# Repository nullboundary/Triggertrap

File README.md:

# Triggertrap Source Code

Triggertrap is an open-source camera triggering platform based on Arduino. 

It comes in two versions: Triggertrap v1 (TTv1), which is a device aimed at consumers; and Triggertrap Shield for Arduino (TT-k) which is aimed at advanced users, hackers, and geeks (like us!). 

The codebase you are looking at is for both the above devices. 

_NOTE_ - there *are* differences between the TTv1 and TT-k. By default, the code ships for the Triggertrap Shield for Arduino (TT-k), because we anticipate that most people downloading and using this code will be using the Triggertrap Shield. If you wish to compile and install this code on your TTv1 device, remember to go into TTConfig.h, and read the section *Choose your version of the Triggertrap*. 

## Triggertrap v1 (TTv1)

The Triggertrap v1 is a battery-powered device with several sensors built-in:

* Laser sensor
* Ambient Light sensor
* Sound sensor

It also has a fully configurable AUX port, in the shape of a RCA socket, designed to accept additional external inputs and sensors. 

_Form Factor_ - The Triggertrap v1 comes in a perspex casing, and uses touch-sensitive buttons for control and operation. 

## Triggertrap Shield for Arduino (TT-k)

The Triggertrap Shield for Arduino is an Arduino-powered device with several sensors built-in:

* Laser sensor
* Ambient Light sensor
* Sound sensor

It also has a fully configurable AUX port, in the shape of a RCA socket, designed to accept additional external inputs and sensors. 

_Form Factor_ - The Triggertrap Shield for Arduino is an Arduino shield, and uses physical buttons for its interface. 

# Open Source & Licencing information 

This file is part of Triggertrap. See Triggertrap.com for more information.

Triggertrap is free software: you can redistribute it and/or modify it under the terms of the GNU General Public License as published by the Free Software Foundation, either version 3 of the License, or (at your option) any later version.
 
Triggertrap is distributed in the hope that it will be useful, but WITHOUT ANY WARRANTY; without even the implied warranty of MERCHANTABILITY or FITNESS FOR A PARTICULAR PURPOSE.  See the GNU General Public License for more details.

You should have received a copy of the GNU General Public License along with Triggertrap. If not, see <http://www.gnu.org/licenses/>.

## Restrictions

The only thing we are keeping control over is the Triggertrap trademarks (name and logo). Full details of the Triggertrap licence is available on http://triggertrap.com/license/ 

# Changenotes

## 0.3.36 (6 March 2013)
* Bugfix: IR signal overflow fix for Nikon cameras when using shield only.
* Bugfix: Adjustment to IR timings for Sony cameras.
* Enhancement: Integration of Timelapse modifications from Duane Cassone. 

## 0.3.35 (16 July 2012)

* Bugfix: Fixes a tiny bug where the screen contrast (menu option added in 0.3.35) wasn't saved to EEPROM properly. 
* Bugfix: Elegant little hack that reads the LCD contrast setting twice, discarding the first reading, ensuring that the readings are accurate, especially when Triggertrap wakes from sleep. 
* Tagging with 0.3.35

## 0.3.34 (9 July 2012)

* Formally introduces Bulb Ramping into the Triggertrap Firmware
* Adds a menu item for adjusting your screen contrast for TTv1 (System -> Contrast)
* Bugfix: Fixes sleep problem introduced in 0.3.33b
* Tidies up code in TriggerTrap.cpp for easier hackability & readability

## 0.3.33b (18 June 2012)

* Introduces the Bulb Ramping feature
* Breaks several other features ;) (that is why this version was only ever a beta...)

## 0.3.32 (23 March 2012)

* Fixes a bug in the production Triggertrap where the laser sensor was too sensitive
* Fixes a bug in the production Triggertrap where the LCD display came up way too dark
* Adds additional documentation licence information that was missed out in the initial release
* Removes accidentally included .DS_Store files

## 0.3.31 (21 March 2012)

First open-source release of the Triggertrap codebase.

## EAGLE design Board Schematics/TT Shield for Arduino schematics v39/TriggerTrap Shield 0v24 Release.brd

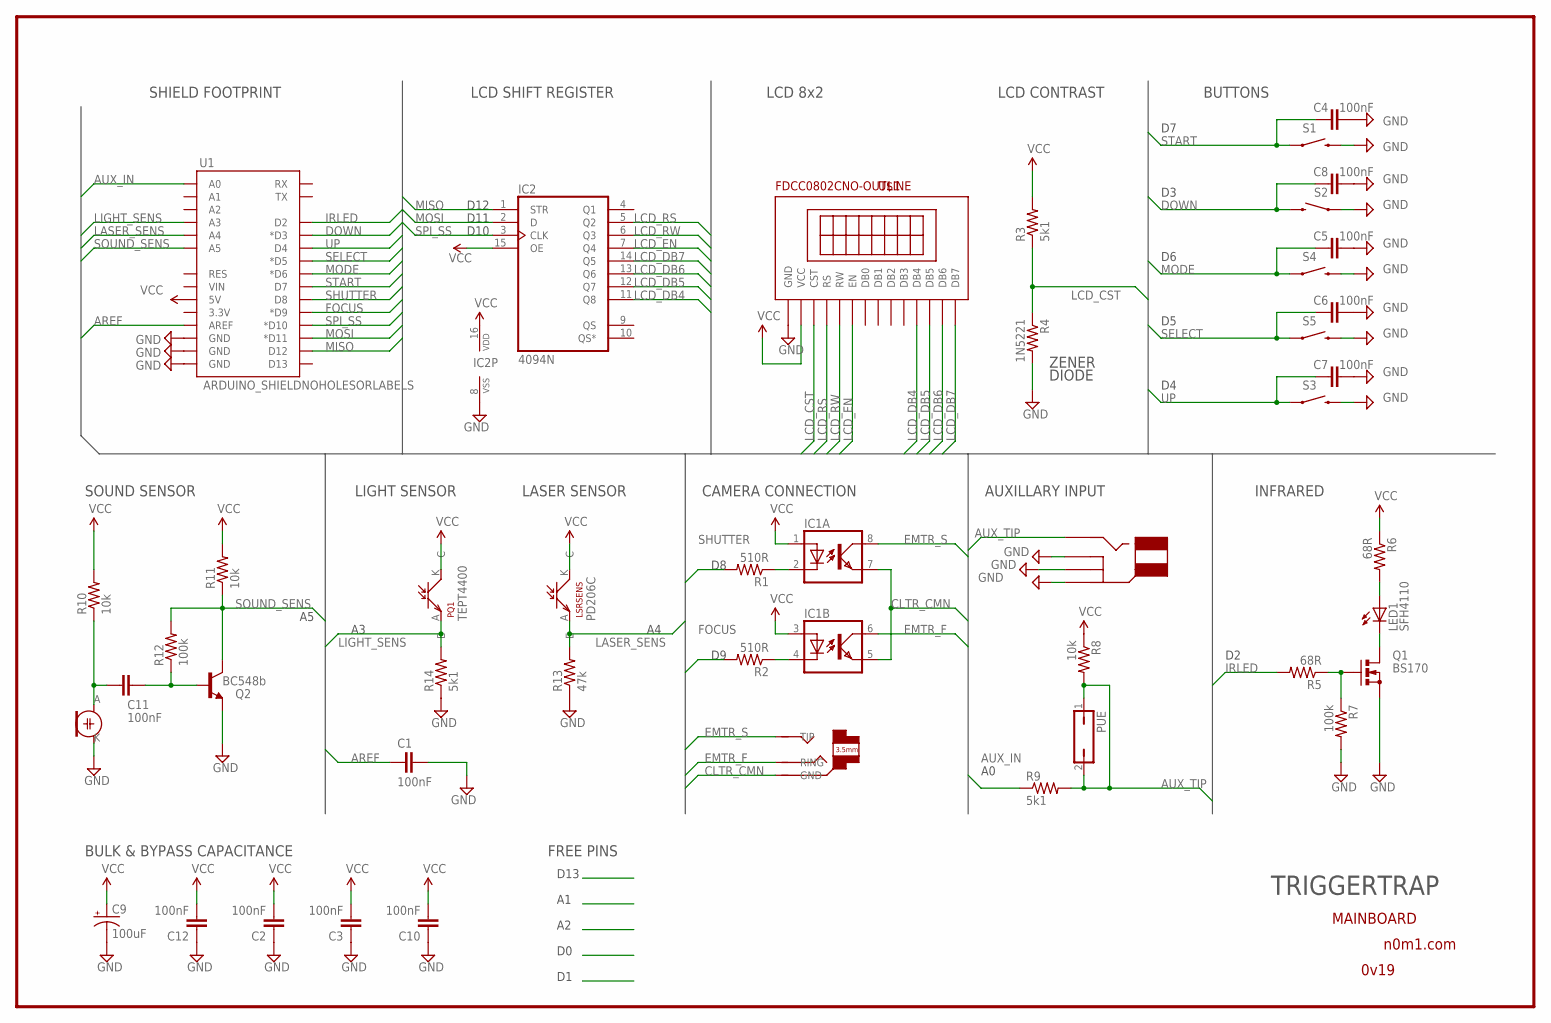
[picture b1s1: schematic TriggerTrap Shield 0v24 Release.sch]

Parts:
AUX: CUI_RCJ-017-RCA; RCA_CUI_RCJ-017
C1, C2, C3, C4, C5, C6, C7, C8, C10, C11, C12: 100nF; C050-024X044
C9: 100uF; TT2D7L
CAM: AUDIO_3.5MM_L_3523; AUDIO_3.5MM_LONG
IC1: LTV826SMLPADS; DIL08-SMLPADS
IC2: 4094N; DIL16
LED1: SFH4110; SIDE_LED
LSRSENS: PD204-6C; LSR-SNS-3MM
MIC: MIC; MIC-254-ECM94-RO
PQ1: TEPT4400; LED-3MM
PUE: JP1Q; JP1
Q1: BS170; SOT54E
Q2: BC548b; SOT54E
R1, R2: 510R; 0204/5
R3, R9, R14: 5k1; 0204/5
R4: 1N5221; 0204/5
R5, R6: 68R; 0204/5
R7, R12: 100k; 0204/5
R8, R10, R11: 10k; 0204/5
R13: 47k; 0204/5
S1: SWITCH-MOMENTARY-212MM; TACTILE-PTH-12MM
S2, S3, S4, S5: SWITCH-MOMENTARY-2PTH; TACTILE-PTH
U1: ARDUINO_SHIELDNOHOLESORLABELS; DUEMILANOVE_SHIELD_NOHOLES_NOLABELS
U$1: FDCC0802CNO-OUTLINE; 8X2-TOPLCD-NOOUTLINE

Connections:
AREF: C1.2, U1.AREF
AUX_IN: R9.1, U1.A0
AUX_TIP: AUX.P$4 (TIP), PUE.1, PUE.2, R8.2, R9.2
CLTR_CMN: CAM.P$1 (GND), IC1.5 (EMIT), IC1.7 (EMIT)
DOWN: C8.1, S2.3 (2), U1.D3 (*D3)
EMTR_F: CAM.P$3 (RING), IC1.6 (COL)
EMTR_S: CAM.P$2 (TIP), IC1.8 (COL)
FOCUS: R2.2, U1.D9 (*D9)
GND: AUX.P$1 (GND1), AUX.P$2 (GND2), AUX.P$3 (GND), C1.1, C2.1, C3.1, C4.2, C5.2, C6.2, C7.2, C8.2, C9.-, C10.1, C12.1, IC2.8 (VSS), MIC.K, Q1.S, Q2.S (E), R4.2, R7.2, R13.1, R14.1, S1.3 (2), S2.1, S3.3 (2), S4.3 (2), S5.3 (2), U1.GND@0 (GND), U1.GND@1 (GND), U1.GND@2 (GND), U$1.P$1 (GND)
IRLED: R5.2, U1.D2
LASER_SENS: LSRSENS.A (E), R13.2, U1.A4
LCD_CST: R3.1, R4.1, U$1.P$3 (CST)
LCD_DB4: IC2.11 (Q8), U$1.P$11 (DB4)
LCD_DB5: IC2.12 (Q7), U$1.P$12 (DB5)
LCD_DB6: IC2.13 (Q6), U$1.P$13 (DB6)
LCD_DB7: IC2.14 (Q5), U$1.P$14 (DB7)
LCD_EN: IC2.7 (Q4), U$1.P$6 (EN)
LCD_RS: IC2.5 (Q2), U$1.P$4 (RS)
LCD_RW: IC2.6 (Q3), U$1.P$5 (RW)
LIGHT_SENS: PQ1.A (E), R14.2, U1.A3
MISO: IC2.1 (STR), U1.D12
MODE: C5.1, S4.1, U1.D6 (*D6)
MOSI: IC2.2 (D), U1.D11 (*D11)
unnamed: C11.1, MIC.A, R10.1
unnamed: LED1.K (C), Q1.D
unnamed: LED1.A, R6.2
unnamed: Q1.G, R5.1, R7.1
unnamed: C11.2, Q2.G (B), R12.1
unnamed: IC1.4 (C), R2.1
unnamed: IC1.2 (C), R1.1
SELECT: C6.1, S5.1, U1.D5 (*D5)
SHUTTER: R1.2, U1.D8
SOUND_SENS: Q2.D (C), R11.1, R12.2, U1.A5
SPI_SS: IC2.3 (CLK), U1.D10 (*D10)
START: C4.1, S1.1, U1.D7
UP: C7.1, S3.1, U1.D4
VCC: C2.2, C3.2, C9.+, C10.2, C12.2, IC1.1 (A), IC1.3 (A), IC2.15 (OE), IC2.16 (VDD), LSRSENS.K (C), PQ1.K (C), R3.2, R6.1, R8.1, R10.2, R11.2, U1.5V, U$1.P$2 (VCC)

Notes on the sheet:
BULK & BYPASS CAPACITANCE
CAMERA CONNECTION
INFRARED
AUXILLARY INPUT
TRIGGERTRAP
MAINBOARD
n0m1.com
0v19
D10
D11
D12
SHIELD FOOTPRINT
LCD 8x2
LCD CONTRAST
LCD SHIFT REGISTER
SOUND SENSOR
LASER SENSOR
LIGHT SENSOR
BUTTONS
FREE PINS
D13
ZENER
DIODE
TEPT4400
PD206C

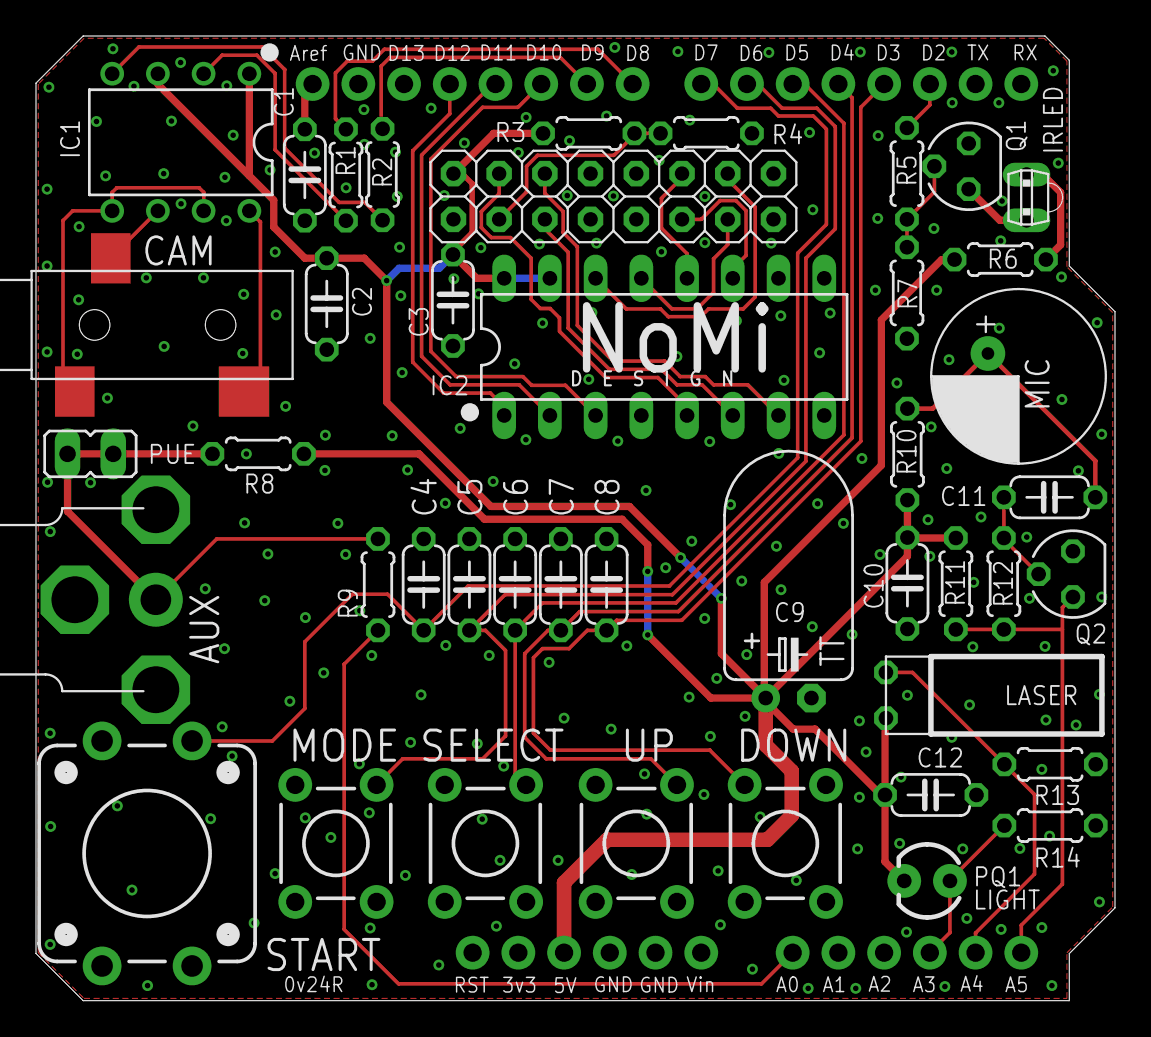
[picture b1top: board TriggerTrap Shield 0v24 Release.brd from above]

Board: 2 copper layers, 59.9 x 53.6 mm, 44 parts (1 on the bottom side), 37 nets.

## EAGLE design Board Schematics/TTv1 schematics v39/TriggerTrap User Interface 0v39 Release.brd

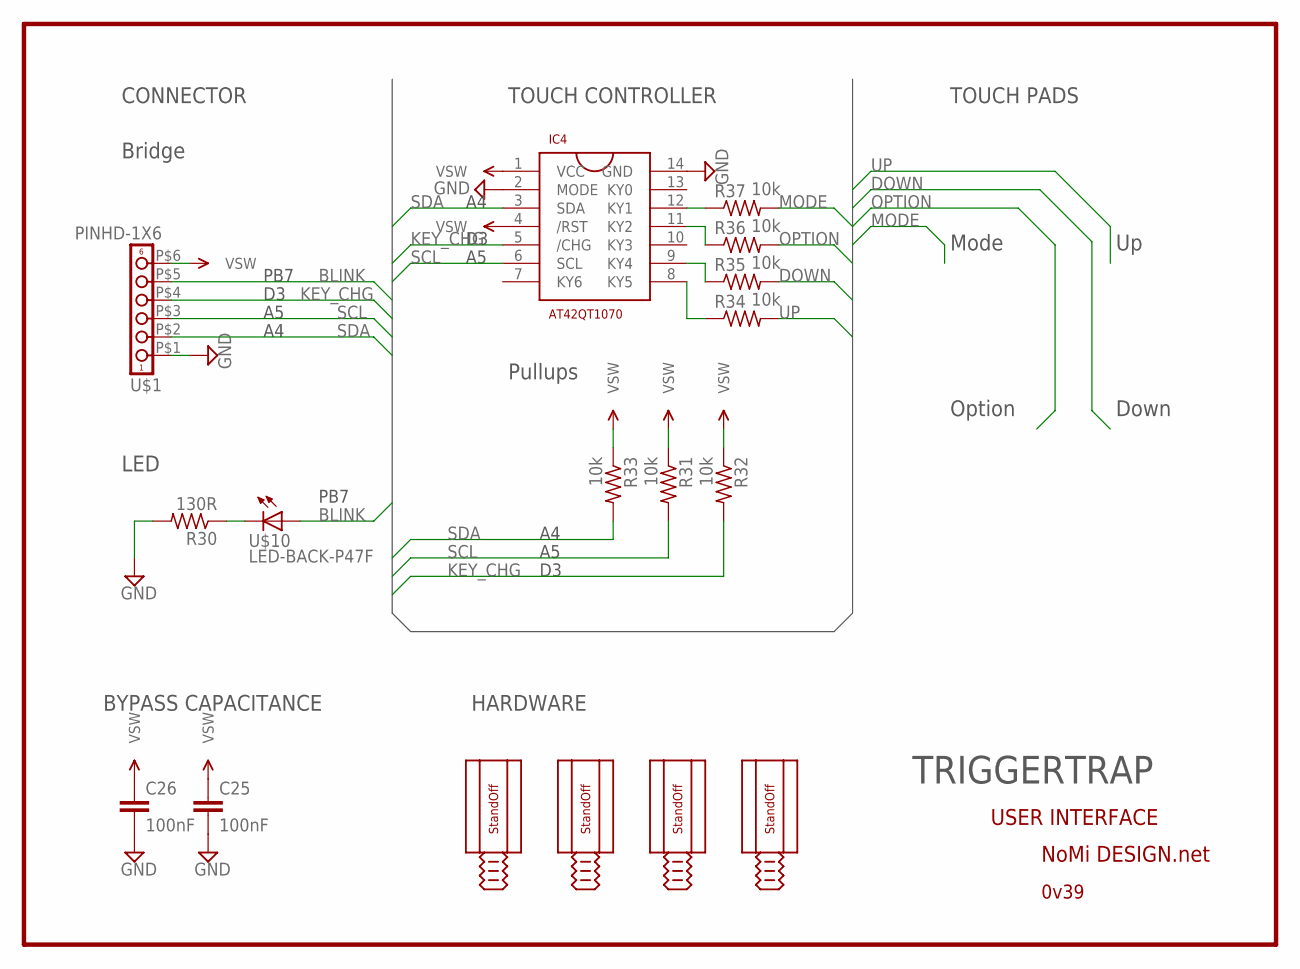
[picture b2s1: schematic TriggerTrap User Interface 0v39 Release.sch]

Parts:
C25, C26: 100nF; C0603K
IC4: AT42QT1070; 14SOIC
R30: 130R; R0603
R31, R32, R33, R34, R35, R36, R37: 10k; R0603
U$1: PINHD-1X6; PINHD-1X6-SMD
U$2, U$23, U$24, U$25: STAND-0FF-3.2; STAND-OFF
U$10: LED-BACK-P47F; LED-P47F

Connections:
BLINK: U$1.P$5 (5), U$10.A
DOWN: R35.2
GND: C25.2, C26.2, IC4.2 (MODE), IC4.14 (GND), R30.2, U$1.P$1 (1)
KEY_CHG: IC4.5 (/CHG), R32.2, U$1.P$4 (4)
MODE: R37.2
unnamed: IC4.12 (KY1), R37.1
unnamed: IC4.11 (KY2), R36.1
unnamed: IC4.9 (KY4), R35.1
unnamed: IC4.8 (KY5), R34.1
unnamed: R30.1, U$10.C
OPTION: R36.2
SCL: IC4.6 (SCL), R31.2, U$1.P$3 (3)
SDA: IC4.3 (SDA), R33.2, U$1.P$2 (2)
UP: R34.2
VSW: C25.1, C26.1, IC4.1 (VCC), IC4.4 (/RST), R31.1, R32.1, R33.1, U$1.P$6 (6)

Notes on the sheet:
Bridge
HARDWARE
BYPASS CAPACITANCE
TOUCH CONTROLLER
LED
TRIGGERTRAP
USER INTERFACE
NoMi DESIGN.net
0v39
PB7
CONNECTOR
TOUCH PADS
Mode
Down
Option
Pullups

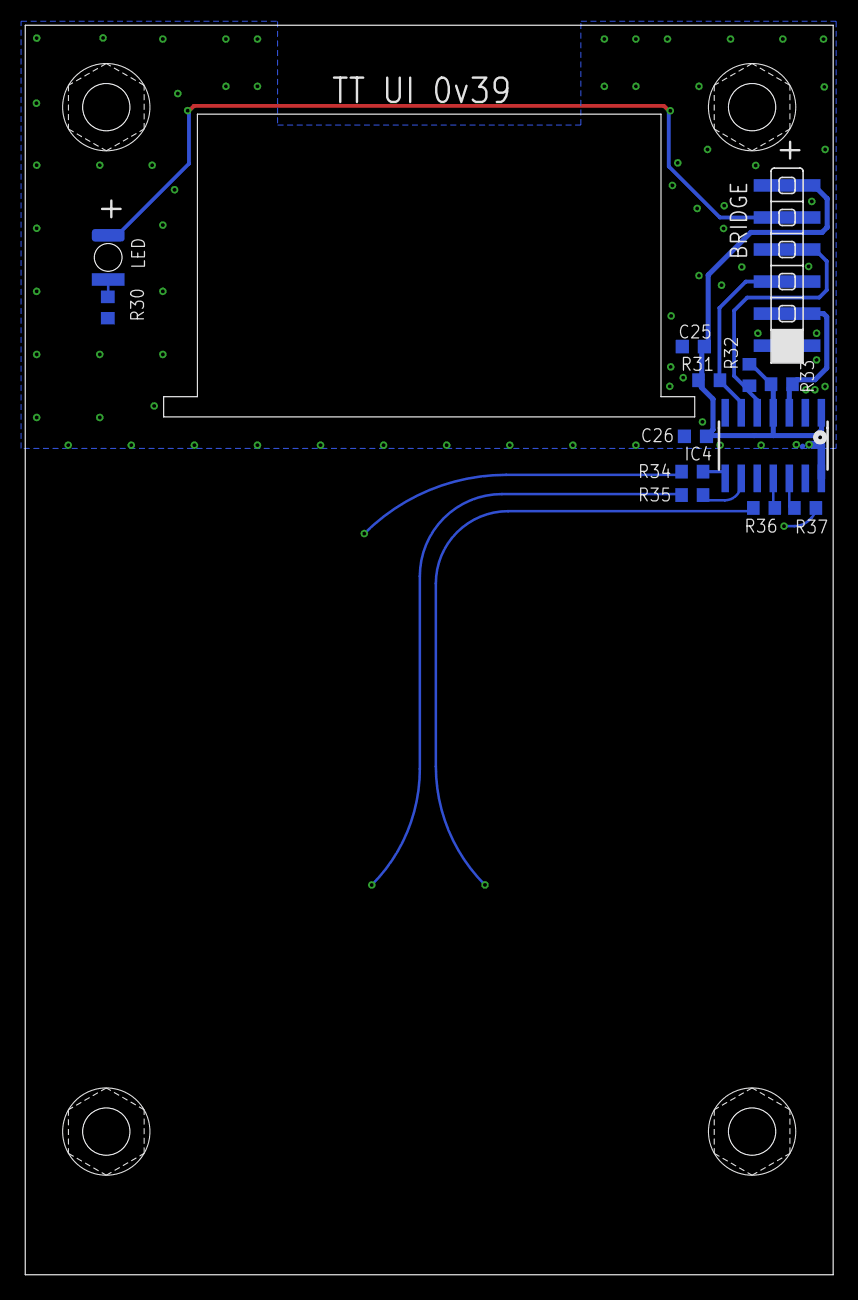
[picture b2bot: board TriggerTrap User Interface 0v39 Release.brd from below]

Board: 2 copper layers, 64.0 x 99.0 mm, 17 parts (17 on the bottom side), 11 nets.

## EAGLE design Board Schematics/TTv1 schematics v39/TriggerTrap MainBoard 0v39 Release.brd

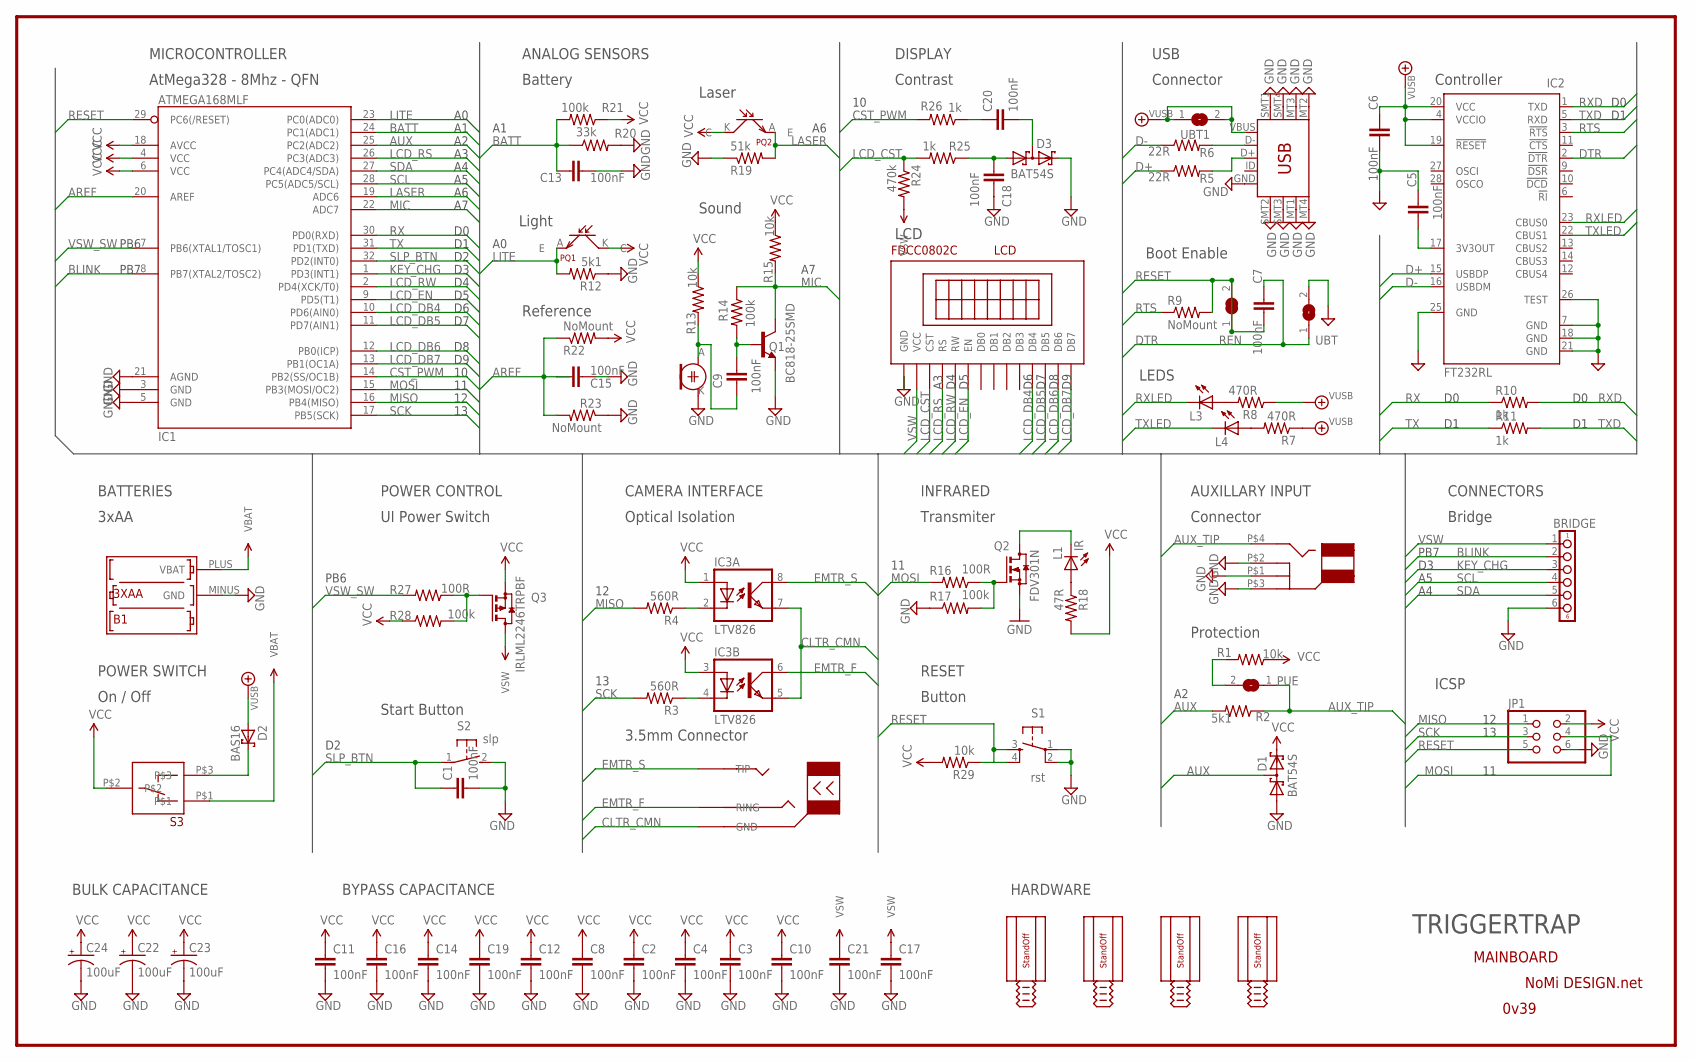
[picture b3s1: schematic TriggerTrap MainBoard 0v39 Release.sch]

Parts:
AUXJACK: CUI_RCJ-017-RCA; RCA_CUI_RCJ-017
B1: 3XAA; 3XAA-CASE
BRIDGE: PINHD-1X6; 1X06
C1, C2, C3, C4, C5, C6, C7, C8, C9, C10, C11, C12, C13, C14, C15, C16, C17, C18, C19, C20, C21: 100nF; 0603-CAP
C22, C23, C24: 100uF; E2,5-7
CAMJACK: AUDIO_3.5MM_L_3523; AUDIO_3.5MM_LONG
D1, D3: BAT54S; SOT23
D2: BAS16; SOT23
IC1: ATMEGA168MLF; MLF32
IC2: FT232RL; SSOP28
IC3: LTV826; DIL08R
JP1: PINHD-2X3/90; 2X03/90
L1: IR; SIDE_LED
L3, L4: LEDCHIPLED_0805; CHIPLED_0805
LCD: FDCC0802C; 8X2-TOPLCD
M1: 254-ECM94-RO; MIC-254-ECM94-RO
PQ1: TEPT4400; LED-3MM
PQ2: EL-PT204-6C; LSR-SNS-3MM
PUE: SJ
Q1: BC818-25SMD; SOT23-BEC
Q2: FDV301N; SOT23
Q3: IRLML2246TRPBF; SOT23
R1, R29: 10k; 0603-RES
R2, R12: 5k1; 0603-RES
R3, R4: 560R; 0603-RES
R5, R6: 22R; R0603
R7, R8: 470R; R0603
R9, R22, R23: NoMount; R0603
R10, R11, R25, R26: 1k; R0603
R13, R15: 10k; R0603
R14, R17, R21, R28: 100k; R0603
R16, R27: 100R; R0603
R18: 47R; 0603-RES
R19: 51k; 0603-RES
R20: 33k; R0603
R24: 470k; R0603
REN: SJ
S1: rst; TACTILE_SWITCH_SMD
S2: slp; B3F-31XX
S3: OS102011MA1QN1
U$2, U$23, U$24, U$25: STAND-0FF-3.2; STAND-OFF
UBT, UBT1: SJ
USB: USB-MICRO-B-SMD; USB-MICROB-SMD

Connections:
AREF: C15.1, IC1.20 (AREF), R22.1, R23.2
AUX: D1.3 (C1A2), IC1.25 (PC2(ADC2)), R2.2
AUX_TIP: AUXJACK.P$4 (TIP), PUE.1, R2.1
BATT: C13.1, IC1.24 (PC1(ADC1)), R20.1, R21.2
BLINK: BRIDGE.2, IC1.8 (PB7(XTAL2/TOSC2))
CLTR_CMN: CAMJACK.P$1 (GND), IC3.5 (EMIT), IC3.7 (EMIT)
CST_PWM: IC1.14 (PB2(SS/OC1B)), R26.2
D+: IC2.15 (USBDP), R5.1
D-: IC2.16 (USBDM), R6.1
DTR: C7.1, IC2.2 (!DTR), UBT.1
EMTR_F: CAMJACK.P$3 (RING), IC3.6 (COL)
EMTR_S: CAMJACK.P$2 (TIP), IC3.8 (COL)
GND: AUXJACK.P$1 (GND1), AUXJACK.P$2 (GND2), AUXJACK.P$3 (GND), B1.MINUS (GND), BRIDGE.6, C1.2, C2.2, C3.2, C4.2, C5.1, C6.2, C8.2, C10.2, C11.2, C12.2, C13.2, C14.2, C15.2, C16.2, C17.2, C18.1, C19.2, C21.2, C22.-, C23.-, C24.-, D1.1 (A1), D3.2 (C2), IC1.3 (GND), IC1.5 (GND), IC1.21 (AGND), IC2.7 (GND), IC2.18 (GND), IC2.21 (GND), IC2.25 (GND), IC2.26 (TEST), JP1.6, LCD.P$1 (GND), M1.K, Q1.E, Q2.2 (S), R12.1, R17.1, R19.1, R20.2, R23.1, S1.1, S1.2, S2.2 (S), UBT.2, USB.GND, USB.MT1 (MTN1), USB.MT2 (MTN2), USB.MT3 (MTN3), USB.MT4 (MTN4), USB.SMT1, USB.SMT2, USB.SMT3, USB.SMT4
KEY_CHG: BRIDGE.3, IC1.1 (PD3(INT1))
LASER: IC1.19 (ADC6), PQ2.A (E), R19.2
LCD_CST: LCD.P$3 (CST), R24.1, R25.2
LCD_DB4: IC1.10 (PD6(AIN0)), LCD.P$11 (DB4)
LCD_DB5: IC1.11 (PD7(AIN1)), LCD.P$12 (DB5)
LCD_DB6: IC1.12 (PB0(ICP)), LCD.P$13 (DB6)
LCD_DB7: IC1.13 (PB1(OC1A)), LCD.P$14 (DB7)
LCD_EN: IC1.9 (PD5(T1)), LCD.P$6 (EN)
LCD_RS: IC1.26 (PC3(ADC3)), LCD.P$4 (RS)
LCD_RW: IC1.2 (PD4(XCK/T0)), LCD.P$5 (RW)
LITE: IC1.23 (PC0(ADC0)), PQ1.A (E), R12.2
MIC: IC1.22 (ADC7), Q1.C, R14.1, R15.2
MISO: IC1.16 (PB4(MISO)), JP1.1, R4.2
MOSI: IC1.15 (PB3(MOSI/OC2)), JP1.4, R16.2
unnamed: C9.1, M1.A, R13.2
unnamed: L1.K (C), Q2.3 (D)
unnamed: C20.1, R26.1
unnamed: L1.A, R18.1
unnamed: C20.2, D3.3 (C1A2)
unnamed: D2.3 (C), S3.P$3
unnamed: Q2.1 (G), R16.1, R17.2
unnamed: L3.A, R8.2
unnamed: L4.A, R7.2
unnamed: C9.2, Q1.B, R14.2
unnamed: IC3.4 (C), R3.1
unnamed: Q3.1 (G), R27.1, R28.2
unnamed: IC3.2 (C), R4.1
unnamed: C18.2, D3.1 (A1), R25.1
unnamed: PUE.2, R1.2
unnamed: C5.2, IC2.17 (3V3OUT)
unnamed: R6.2, USB.D-
unnamed: R5.2, USB.D+
RESET: C7.2, IC1.29 (PC6(/RESET)), JP1.5, R9.2, R29.1, REN.1, REN.2, S1.3, S1.4
RTS: IC2.3 (!RTS), R9.1
RX: IC1.30 (PD0(RXD)), R10.1
RXD: IC2.1 (TXD), R10.2
RXLED: IC2.23 (CBUS0), L3.C
SCK: IC1.17 (PB5(SCK)), JP1.3, R3.2
SCL: BRIDGE.4, IC1.28 (PC5(ADC5/SCL))
SDA: BRIDGE.5, IC1.27 (PC4(ADC4/SDA))
SLP_BTN: C1.1, IC1.32 (PD2(INT0)), S2.1
TX: IC1.31 (PD1(TXD)), R11.1
TXD: IC2.5 (RXD), R11.2
TXLED: IC2.22 (CBUS1), L4.C
VBAT: B1.PLUS (VBAT), S3.P$1
VCC: C2.1, C3.1, C4.1, C8.1, C10.1, C11.1, C12.1, C14.1, C16.1, C19.1, C22.+, C23.+, C24.+, D1.2 (C2), IC1.4 (VCC), IC1.6 (VCC), IC1.18 (AVCC), IC3.1 (A), IC3.3 (A), JP1.2, PQ1.K (C), PQ2.K (C), Q3.2 (S), R1.1, R13.1, R15.1, R18.2, R21.1, R22.2, R28.1, R29.2, S3.P$2
VSW: BRIDGE.1, C17.1, C21.1, LCD.P$2 (VCC), Q3.3 (D), R24.2
VSW_SW: IC1.7 (PB6(XTAL1/TOSC1)), R27.2
VUSB: C6.1, D2.1 (A), IC2.4 (VCCIO), IC2.19 (!RESET), IC2.20 (VCC), R7.1, R8.1, UBT1.1, UBT1.2, USB.VBUS

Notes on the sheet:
MICROCONTROLLER
BATTERIES
BULK CAPACITANCE
POWER SWITCH
BYPASS CAPACITANCE
CAMERA INTERFACE
POWER CONTROL
ANALOG SENSORS
Sound
INFRARED
USB
Boot Enable
HARDWARE
RESET
AUXILLARY INPUT
ICSP
LEDS
CONNECTORS
TRIGGERTRAP
MAINBOARD
NoMi DESIGN.net
0v39
PB6
PB7
UI Power Switch
Start Button
Optical Isolation
3.5mm Connector
Battery
AtMega328 - 8Mhz - QFN
Reference
Transmiter
3xAA
On / Off
Laser
Light
Button
DISPLAY
Contrast
LCD

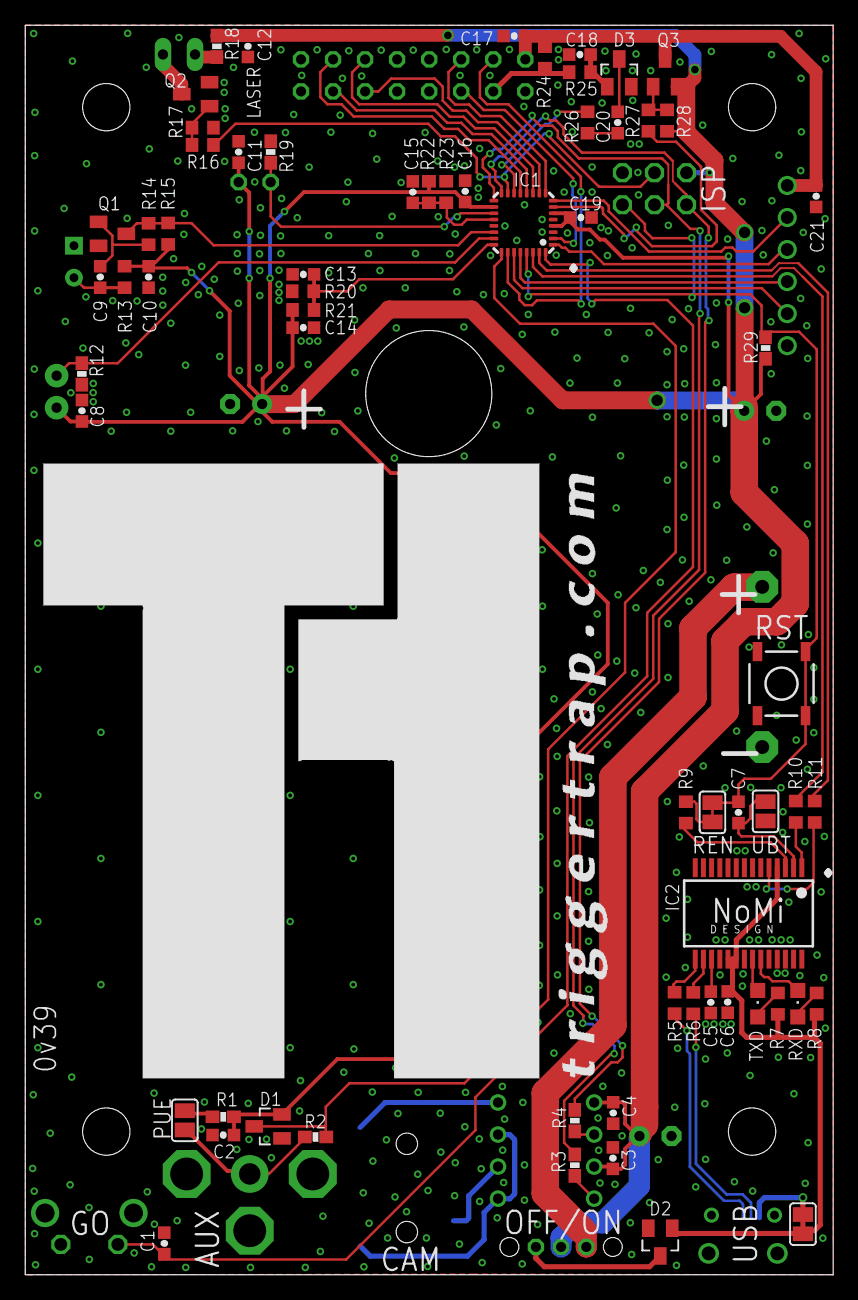
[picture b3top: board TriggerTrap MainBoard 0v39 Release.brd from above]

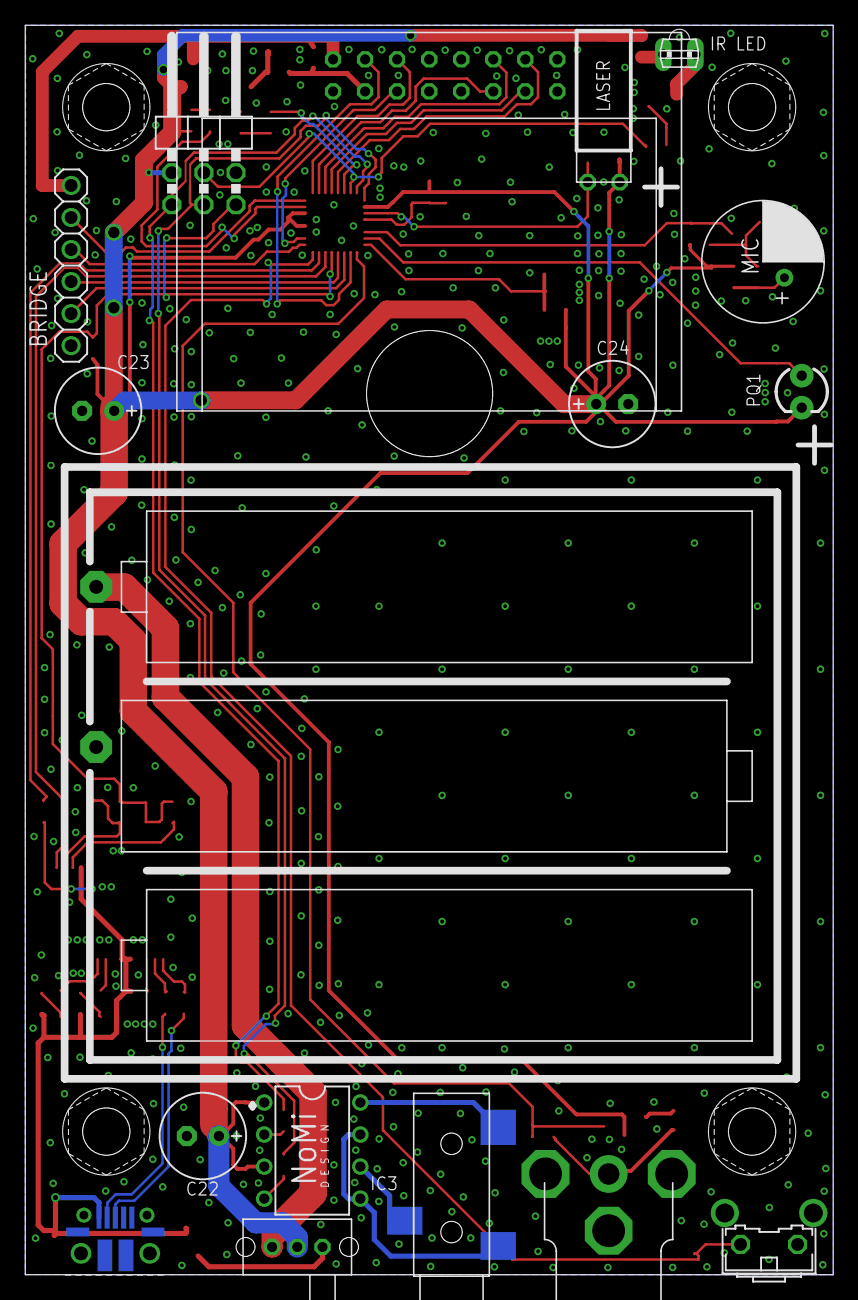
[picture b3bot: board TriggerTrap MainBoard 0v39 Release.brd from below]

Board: 2 copper layers, 64.0 x 99.0 mm, 86 parts (20 on the bottom side), 62 nets.

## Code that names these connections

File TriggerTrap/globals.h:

/************************************************************************************
 * 	
 * 	Name    : Trigger Trap globals.h                         
 * 	Author  : Noah Shibley, NoMi Design                         
 * 	Date    : July 10th 2011                                    
 * 	Version : 0.1                                              
 * 	Notes   : Where all the constants (defines) are located           
 * 
 * 	 Copyright (c) 2011 NoMi Design All right reserved.
 * 
 *     
 *
 * 
 * 	This file is part of Trigger Trap.
 * 
 * 		    Trigger Trap is free software: you can redistribute it and/or modify
 * 		    it under the terms of the GNU General Public License as published by
 * 		    the Free Software Foundation, either version 3 of the License, or
 * 		    (at your option) any later version.
 * 
 * 		    Trigger Trap is distributed in the hope that it will be useful,
 * 		    but WITHOUT ANY WARRANTY; without even the implied warranty of
 * 		    MERCHANTABILITY or FITNESS FOR A PARTICULAR PURPOSE.  See the
 * 		    GNU General Public License for more details.
 * 
 * 		    You should have received a copy of the GNU General Public License
 * 		    along with Trigger Trap.  If not, see <http://www.gnu.org/licenses/>.
 * 
 ***********************************************************************************/

#ifndef GLOBALS_H
#define GLOBALS_H

#include <WProgram.h>  //Analog #defines A0,A1 etc. 

// PIN usage and setup

//const int LASER_SENSOR = A0; 			// A0 = Analong in - Laser Sensor
//const int AMBIENT_LIGHT_SENSOR = A1;	// A1 = Analong in - Ambient Light Sensor
//const int AUX = A2;						// A2 = Analong in - AUX in
//const int POWER_UI = A3;				// A3 = Digital out - UI power mosfet switch
const int SDA_TOUCH = A4;				// A4 = I2C bus - SDA - touch controller  
const int SCL_TOUCH = A5;				// A5 = I2C bus - SCL - touch controller  
//const int SOUND_IN = A6;				// A6 = Analong in - Sound in    
const int BATT_VOLTS = A7;				// A7 = Analong in - Battery voltage in    

const int SERIAL_RX = 0;				// D0 = Serial RXD
const int SERIAL_TXD = 1;				// D1 = Serial TXD
//const int START_BUTTON = 2;				// D2 = Digital in - Start button 
//const int KEY_CHANGE = 3; 				// D3 = Digital in - key change interrupt for touch ic
//const int KEY_PAD_LEDS = 4;				// D4 = Digital out - LED on keypad
const int LCD_ENABLE = 5; 				// D5 = Digital out - LCD Enable 
const int LCD_DATALINE4 = 6;			// D6 = Digital out - LCD Dataline 4
const int LCD_DATALINE5 = 7;			// D7 = Digital out - LCD Dataline 5
const int LCD_DATALINE6 = 8;			// D8 = Digital out - LCD Dataline 6 
const int LCD_DATALINE7 = 9; 			// D9 = Digital out - LCD Dataline 7 
//const int SPEAKER_OUT = 10;				// D10 = Digital out - Speaker
//const int INFRARED_SENDER = 11;			// D11 = Digital out - Infrared sender
//const int CAMERA_TRIGGER_A = 12;		// D12 = Digital out - Camera Trigger A
//const int CAMERA_TRIGGER_B = 13;		// D13 = Digital out - Camera Trigger B

int triggerMode = 0; //which function is being used now

const int NUM_MODES = 5; //number of trigger modes
const int TIMELAPSE_MODE = 3; 
const int LASER_MODE = 0;
const int SOUND_MODE = 1;
const int LIGHT_MODE = 2;
const int AUX_MODE = 4;
const int MAN_MODE = 5;





boolean trapActive = false;

	int timeLapseInterval = 0;
	unsigned long prevTime = 2147483647;  //prevent triggering, if start button not pressed for 25 days..

unsigned long const MAX_NUM_SHOTS = 2147483647; //many more then your SD card can do
unsigned int const MAX_INTERVAL = 86400; //24 hours





// PB6 = Digital in - LCD RS
// PB7 = Digital out - LCD RW

int freq =100; 
int start =0;


#endif

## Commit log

2011-08-26 readme
2011-08-26 First project commit
2011-08-26 changed TriggerTrap.pde name
2011-08-26 deleted TriggerTrap02.pde
2011-08-30 added delay option functionality
2011-08-31 Updated for delay, and redefined how the trigger function works, and is used
2011-08-31 bug fixed for delay in timelapse
2011-09-15 updates for 0v34 board
2011-09-15 added LCD, many bugs remain
2011-09-16 LCD working, Touch Chip Reset, c style str concats
    LCD is now fully working, the TTUI library now extends Liquid Crystal
    Lib. Also AtTouch now resets the touch chip in the library begin()
    function. In case the mcu reset, but the touch chip did not. Delay time
    formatting now uses strcat instead of arduino String. Aux.h and cpp
    were changed to auxiliary.h and cpp because of crazy windows 7 not
    allowing files named aux.h !
2011-09-16 start button and UI power On/Off should be working
    UI power off works, and probably power ON. However my start button is
    not working…could be a hardware problem? Bad solder joint?
2011-09-19 Minor changes to LCD. Power on, and power off not working but errors are commented out
2011-09-19 Changed LCD menu formatting, and added threshold sensor level feedback
    Sensor level is not displayed on the LCD when you try to set the
    threshold. Its a little confusing, maybe we need to label the
    difference between sensor level and threshold setting. However this is
    not much space...
2011-09-19 got rid of an extra aux.h file that was not suppose to be there
2011-09-20 Optimized for SRAM size, SRAM now 763 bytes. Also made some variables into unsigned ints to contain large values like for time delay and delta
2011-09-21 Added feature to give feedback when Trigger is active. Also switched to LiquidCrystalFast library
    Should see LCD feedback when trap is active in USB power mode.
2011-09-22 Set speed limit for press and hold. Added high speed limit if you hold for 10secs. Debugged a few things
2011-09-24 Formatting, and organization of code
2011-09-25 fixed small syntax error, in trigger.cpp
2011-09-26 Many small bug fixes, closed issue #5
2011-09-27 Delay added to AtTouch Lib. Fixes the auto calibration time out.
2011-09-27 fixed TTSleep so wdt doesn't reset on timeout, instead it just interrupts
2011-09-27 Switched from Wire lib i2c lib by Wayne Truchsess.
2011-09-29 Added eeprom reset and save states
2011-09-29 Eeprom settings values are now saved and restored. Also start button hold & reset is complete. MCU sleep for time-lapse is started but not complete.
2011-09-30 Added Michael's power up / power down code. bug fixes, and cleaning.
    Sleep currently won't wake up. Only in battery mode.
2011-11-07 Updated PB6&PB7 to atmega328 names PORTB6&PORTB7. Also adde the IRremote lib for use with IR transmitting.
2011-11-08 Added IR shutter codes for Nikon,Pentax,Olympus.
2011-11-08 Added Sony IR codes, and a guess at what could be Cannon RC-6 codes
2011-11-09 fixed some issues related to the WatchDog sleep in the timelapse class.
    Should be working now, however the TT has trouble detecting "battery
    mode" so it doesn't switch into sleep mode
2011-11-10 Fixed time-lapse sleep for battery, it works except for the first shot, which sometimes has the wrong delta.
2011-11-14 Changed the sleep library to a totally new one based on the code by "Cloudy"
    written by "Cloudy" in this post
    http://www.arduino.cc/cgi-bin/yabb2/YaBB.pl?num=1292898715
2011-11-14 oops
2011-11-14 Sleep is now accurate. Time-lapse is almost complete
2011-11-14 added stop() function to trigger, which will tell the UI to stop taking photos. Used for num shot in timelapse
2011-11-16 Lots of bug fixes. Check the issues list on GitHub
2011-11-17 fixed, Camera trigger AB swap bug, small updates to delay lcd display, and IR control
2011-11-18 added millisecond delay. Created millisecond time formatting, updated menu text
2011-11-18 added infinity symbol for time-lapse #shots menu
2011-11-19 added separate shutter reset for A and B triggers, removed IRshutter for testing.
    Also made all the sensors trigger both A and B triggers
2011-11-21 Modified setShutters function, making it easier to setup focus and shutter
2011-11-23 fixed shutter bug, had to set pinmode out for shutter and focus.
2011-11-23 small fix to laser trigger. Related to menus in menuOpts array
2011-11-24 added sensor read out refresh, and updated new TTIRremote library from michael.
2011-11-25 added system setting menu. To set IR, shutter and focus. On/off
2011-11-26 fixed mix up bug between focus and shutter trigger variables
2011-11-26 Revert "fixed mix up bug between focus and shutter trigger variables"
    This reverts commit 9779f53c55137a92760a725f078c5ca2387650aa.
2011-11-26 Fixed a mix up bug between focus and shutter.
    Had a weird error with git client, so the last update and reverts are
    the same as this one. :P
2011-11-26 added auto sleep. If more then 30 seconds pass, the TT sleeps, if its not active
    also fixed a subtle bug in AtTouch library. It was triggering HOLD over
    and over, with key 0 (we have no key 0).. so it wasn't affecting
    anything..but odd.
2011-11-30 Major update. New shutter code, and button press behavior
    the new shutter code separates shutter,focus and IR into totally
    separate independent sections. The new button behavior shows you the
    previous press before updating
2011-12-02 Added RC5 & WLDC100 IR codes. Though they are untested
2011-12-03 Focus always fires now, just how long it fires changes, based on whether its on/off
    I also fixed a bug related to time-lapse sleep. Where the buttons
    wouldn't work for awhile after it wakes.
2011-12-16 TT Shield code added, TTConfig added, lots of restructuring
    There is a new interface class that is a middle layer between all TT
    stuff and your arduino sketch....should to make things cleaner.
2011-12-16 errgh, this is suppose to be deleted, forgot to check it
2011-12-17 Cosmetic & documentation updates
    Adding documentation to the config file, mostly expanding the info
    Changing all instances of 'Trigger Trap' to 'Triggertrap'
2011-12-17 Small fix to the arduino sketch includes
    Weirdest bug ever, arduino ignores /* */ comment tags for the
    includes...
2011-12-18 Revert a75414f5b378ddf4eb68cad3947d0425626548b5^..HEAD
2011-12-18 Added FlipFlop Mode
    This commit adds the FlipFlop mode to the Triggertrap. Per this commit
    it is only a copy of the Timelapse mode. It does work but does nothing
    useful
2012-01-03 Some commenting and tiny bug fixes
2012-01-29 New LCD lib for shield, plus fixes for shield buttons
2012-01-30 updated i2c lib to rev5, added firmware version number
2012-02-03 added interrupts for startbutton on TT Shield
2012-02-06 added Hardware QA test code, also stopped using liquidCrystal fast
    using only newliquidcrystal, not both
2012-03-17 added michaels BitBang IR fix, moved IRRemote lib to inside TT lib.
2012-03-21 v0.3.31 - Initial open source release
    Here goes nothing… This is the first release of the Triggertrap
    codebase released under open source licence.
2012-03-21 Nuke old Readme file
    Whoops, forgot to remove this. Mae culpa.
2012-03-21 Remove DS_Store files
2012-03-22 Small fixes in licence / No functional updates
    Turns out we had missed some of the licence documents that should have
    been included, and some of the files were incorrectly tagged with the
    wrong byline / licence information.
    No functionality has changed in this commit.
2012-03-23 bug fixes to laser and LCD for working with factory production model
2012-03-23 small bug fix to laser threshold setting
2012-03-23 Some additional documentation of the Auxiliary mode
    Additional documentation and a link to the Aux mode section of the user
    manual for further reference.
2012-03-25 updates to fix lcd error
2012-03-25 updated comments in auxiliary.h and cpp
2012-03-30 Updating Config file to reflect new default behaviour
    The standard behaviour has changed: We now assume that people
    downloading the code are doing so because they want to run it on a
    Triggertrap Shield for Arduino. People who are developing on the TTv1,
    need to comment out the #define TT_SHIELD statement in the config file.
    This update amends the in-line help to reflect this change.
2012-06-19 v0.3.33b - Bulb Ramping Beta
    This version of the code adds a beta version of the bulb ramping mode -
    it isn't yet completely polished, but it works. It's a great example of
    how you can add your own modes to the Triggertrap!
2012-06-20 Revert "v0.3.33b - Bulb Ramping Beta"
    This reverts commit b0d9a61a456591df078b66ca6341738c17d16ce9.
2012-06-20 Removing a typo bug in the config file
    My fault entirely - sorry.
2012-06-20 Expanding explanation for Shield / TTv1 switch
2012-07-03 added bulb ramp, numerous structural changes
2012-07-03 many structural changes
2012-07-09 added LCD contrast menu, to adjust contrast settings and save to eeprom
2012-07-09 Triggertrap Firmware v0.3.34
    Adding Bulb Ramping & Contrast control + bugfixes
2012-07-09 Typo in Readme
    Re-adds accidentally removed change notes for 0.3.32
2012-07-16 Triggertrap v0.3.35
    Fixes a small bug where screen contrast readings were wrong after
    waking up from deep sleep.
2012-07-16 Tagging with 0.3.35
2012-08-03 added boards file to create TriggerTrap V1.0 option in the arduino menu
2012-08-15 fixed bug on bulb ramp start/end menus
2012-08-29 Correcting spelling of Triggertrap
    In the boards file, Triggertrap was spelled incorrectly - whoops.
2012-08-30 fixed case - important on Linux where files are case sensitive
2012-08-30 removed unneccessary executable bit
2012-08-30 replaced deprecated prog_char with char PROGMEM
2012-08-30 fixed build error: "const char PROGMEM * XY" are now "const char PROGMEM * const XY"
2012-10-28 Update libraries/TriggerTrap/TTConfig.h
    Updated the reference to the laser sensor - was A3, should be A4.
2013-03-06 Add binaries, because GitHub has deprecated downloads.
2013-03-06 Add gitattributes
2013-03-15 Remove corrupted hexes
2017-06-07 Commit schematics to Github
    schematics used to live on http://triggertrap.com/schematics, but as
    the site went down, the schematics went with them.
